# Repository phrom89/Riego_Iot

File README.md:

# Riego_Iot
Sistema de riego Iot - Proyecto Final 2023

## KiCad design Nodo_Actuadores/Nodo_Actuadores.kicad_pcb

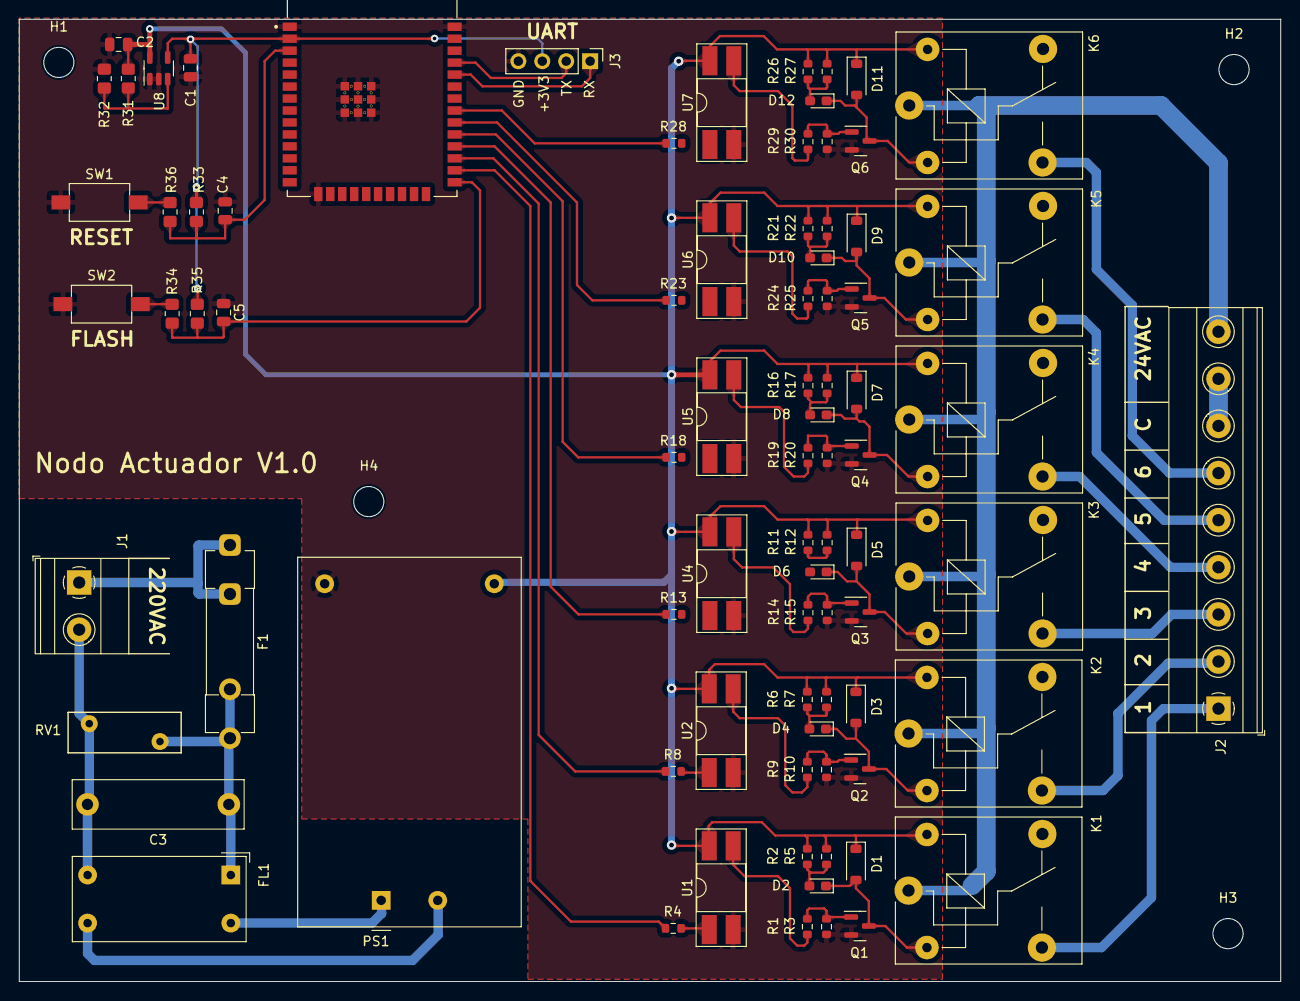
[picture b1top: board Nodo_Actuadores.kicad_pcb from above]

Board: 2 copper layers, 133.9 x 102.1 mm, 86 parts (0 on the bottom side), 59 nets.

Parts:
C1, C2, C4, C5: 0.1uF; C_0805_2012Metric
C3: 0.1uF 275V X2; C_Rect_L18.0mm_W5.0mm_P15.00mm_FKS3_FKP3
D1, D3, D5, D7, D9, D11: 1N4148W; D_SOD-123
D2, D4, D6, D8, D10, D12: TBD; LED_0603_1608Metric_Pad1.05x0.95mm_HandSolder
F1: Fuse; Fuseholder_Clip-5x20mm_Littelfuse_445-030_Inline_P20.50x5.2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
FL1: Choke 12MH 300MA 2LN TH; Choke_Schaffner_RN202-04-8.8x18.2mm
H1, H2, H3, H4: MountingHole; MountingHole_3.2mm_M3_DIN965
J1: Screw_Terminal_01x02; TerminalBlock_Phoenix_MKDS-1,5-2_1x02_P5.00mm_Horizontal
J2: Screw_Terminal_01x09_5mm; TerminalBlock_Phoenix_MKDS-1,5-9_1x09_P5.00mm_Horizontal
J3: Conn_01x04; PinHeader_1x04_P2.54mm_Vertical
K1, K2, K3, K4, K5, K6: SRD-05VDC-SL-C; Relay_SPDT_SANYOU_SRD_Series_Form_C
PS1: HLK-5M05; Converter_ACDC_HiLink_HLK-5Mxx
Q1, Q2, Q3, Q4, Q5, Q6: 2N7002; SOT-23
R1, R9, R14, R19, R24, R29: 1K; R_0603_1608Metric
R2, R4, R5, R6, R7, R8, R11, R12, R13, R16, R17, R18, R21, R22, R23, R26, R27, R28: 100; R_0603_1608Metric
R3, R10, R15, R20, R25, R30: 100K; R_0603_1608Metric
R31, R32: 100k; R_0805_2012Metric_Pad1.20x1.40mm_HandSolder
R33, R35: 10K; R_0805_2012Metric_Pad1.20x1.40mm_HandSolder
R34, R36: 220; R_0805_2012Metric_Pad1.20x1.40mm_HandSolder
RV1: 10D561KTR; RV_Disc_D12mm_W4.3mm_P7.5mm
SW1: Reset; SW_Tactile_SPST_NO_Straight_6x3,5_modificado
SW2: Flash; SW_Tactile_SPST_NO_Straight_6x3,5_modificado
U1, U2, U4, U5, U6, U7: PC817; DIP-4_W8.89mm_SMDSocket_LongPads
U3: ESP32-WROOM-32E__4MB_HIGH_TEMP_; ESP32-WROOM-32E__4MB_HIGH_TEMP
U8: R1524N033B-TR-KE; SOT-23-5

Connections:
24VAC: J2.9, K1.1, K2.1, K3.1, K4.1, K5.1, K6.1
24VAC_COMUN: J2.7, J2.8
+3V3: C1.2, J3.3, R33.1, R35.2, U3.2 (3V3), U8.4 (VOUT)
+5V: C2.2, D1.1 (K), D3.1 (K), D5.1 (K), D7.1 (K), D9.1 (K), D11.1 (K), K1.5, K2.5, K3.5, K4.5, K5.5, K6.5, PS1.4 (+Vout), R2.1, R5.1, R6.1, R7.1, R11.1, R12.1, R16.1, R17.1, R21.1, R22.1, R26.1, R27.1, R31.1, U1.4, U2.4, U4.4, U5.4, U6.4, U7.4, U8.5 (VDD)
/Fuente de alimentacion/L: F1.1, J1.1
/Fuente de alimentacion/N: C3.2, FL1.3, J1.2, RV1.2
/IN1: R4.1, U3.26 (IO4)
/IN2: R8.1, U3.27 (IO16)
/IN3: R13.1, U3.28 (IO17)
/IN4: R18.1, U3.29 (IO5)
/IN5: R23.1, U3.30 (IO18)
/IN6: R28.1, U3.31 (IO19)
GND: C1.1, C2.1, C4.2, C5.1, J3.4, PS1.3 (-Vout), Q1.2 (S), Q2.2 (S), Q3.2 (S), Q4.2 (S), Q5.2 (S), Q6.2 (S), R3.1, R10.1, R15.1, R20.1, R25.1, R30.1, R32.2, SW1.1, SW2.2, U1.2, U2.2, U3.1 (GND), U3.15 (GND), U3.38 (GND), U3.39_1 (GND), U3.39_2 (GND), U3.39_3 (GND), U3.39_4 (GND), U3.39_5 (GND), U3.39_6 (GND), U3.39_7 (GND), U3.39_8 (GND), U3.39_9 (GND), U4.2, U5.2, U6.2, U7.2, U8.1 (GND), U8.2 (GND)
unnamed: C3.1, F1.2, FL1.1, RV1.1
unnamed: D1.2 (A), D2.1 (K), K1.2, Q1.3 (D)
unnamed: D2.2 (A), R2.2, R5.2
unnamed: D3.2 (A), D4.1 (K), K2.2, Q2.3 (D)
unnamed: D4.2 (A), R6.2, R7.2
unnamed: D5.2 (A), D6.1 (K), K3.2, Q3.3 (D)
unnamed: D6.2 (A), R11.2, R12.2
unnamed: D7.2 (A), D8.1 (K), K4.2, Q4.3 (D)
unnamed: D8.2 (A), R16.2, R17.2
unnamed: D10.2 (A), R21.2, R22.2
unnamed: D9.2 (A), D10.1 (K), K5.2, Q5.3 (D)
unnamed: D11.2 (A), D12.1 (K), K6.2, Q6.3 (D)
unnamed: D12.2 (A), R26.2, R27.2
unnamed: J3.1, U3.34 (RXD0)
unnamed: J3.2, U3.35 (TXD0)
unnamed: FL1.2, PS1.1 (AC/L)
unnamed: FL1.4, PS1.2 (AC/N)
unnamed: Q1.1 (G), R1.2, R3.2
unnamed: Q2.1 (G), R9.2, R10.2
unnamed: Q3.1 (G), R14.2, R15.2
unnamed: Q4.1 (G), R19.2, R20.2
unnamed: Q5.1 (G), R24.2, R25.2
unnamed: Q6.1 (G), R29.2, R30.2
unnamed: R1.1, U1.3
unnamed: R4.2, U1.1
unnamed: R8.2, U2.1
unnamed: R9.1, U2.3
unnamed: R13.2, U4.1
unnamed: R14.1, U4.3
unnamed: R18.2, U5.1
unnamed: R19.1, U5.3
unnamed: R23.2, U6.1
unnamed: R24.1, U6.3
unnamed: R28.2, U7.1
unnamed: R29.1, U7.3
unnamed: R34.2, SW2.1
unnamed: R36.1, SW1.2
unnamed: C4.1, R33.2, R36.2, U3.3 (EN)
unnamed: C5.2, R34.1, R35.1, U3.25 (IO0)
unnamed: R31.2, R32.1, U8.3 (CE)
OUT1: J2.1, K1.3
OUT2: J2.2, K2.3
OUT3: J2.3, K3.3
OUT4: J2.4, K4.3
OUT5: J2.5, K5.3
OUT6: J2.6, K6.3

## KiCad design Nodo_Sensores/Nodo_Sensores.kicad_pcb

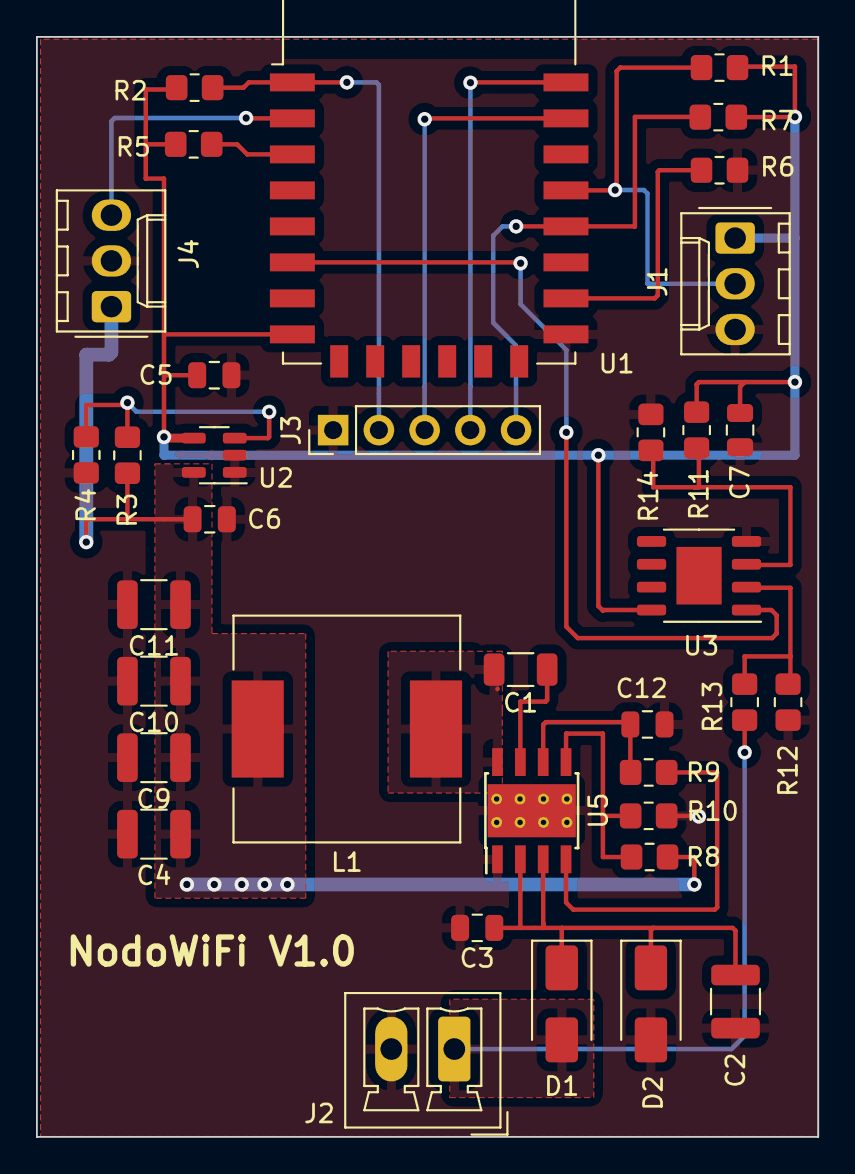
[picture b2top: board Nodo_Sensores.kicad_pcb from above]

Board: 2 copper layers, 43.4 x 61.1 mm, 36 parts (0 on the bottom side), 22 nets.

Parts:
C1: 100nF; C_1206_3216Metric
C2: 10uF; C_1210_3225Metric
C3: 220nF; C_0805_2012Metric
C4, C9, C10, C11: 22uF; C_1210_3225Metric
C5, C6, C7: 0.1uF; C_0805_2012Metric
C12: 1uF; C_0805_2012Metric
D1: SK34A; D_SMA
D2: D; D_SMA
J1, J4: Conn_01x03; Molex_KK-254_AE-6410-03A_1x03_P2.54mm_Vertical
J2: Conn_01x02; PhoenixContact_MCV_1,5_2-G-3.5_1x02_P3.50mm_Vertical
J3: Conn_01x05; PinHeader_1x05_P2.54mm_Vertical
L1: 6.8uH; L_12x12mm_H8mm
R1: 47K; R_0805_2012Metric_Pad1.20x1.40mm_HandSolder
R2, R5, R6, R7: 10K; R_0805_2012Metric_Pad1.20x1.40mm_HandSolder
R3, R4, R8, R9: 100k; R_0805_2012Metric_Pad1.20x1.40mm_HandSolder
R10: 43,2K; R_0805_2012Metric_Pad1.20x1.40mm_HandSolder
R11, R12, R14: 10k; R_0805_2012Metric_Pad1.20x1.40mm_HandSolder
R13: 20k; R_0805_2012Metric_Pad1.20x1.40mm_HandSolder
U1: ESP-12F; ESP-12E
U2: R1524N033B-TR-KE; SOT-23-5
U3: TS3702; SOIC-8-1EP_3.9x4.9mm_P1.27mm_EP2.514x3.2mm
U5: LMR33630ADDA; Texas_HSOP-8-1EP_3.9x4.9mm_P1.27mm_ThermalVias

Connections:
+3.3V: C5.2, C7.1, J1.1, R1.1, R2.1, R5.1, R7.1, R11.1, U1.8 (VCC), U2.4 (VOUT), U3.8 (V+)
+5V: C4.1, C6.2, C9.1, C10.1, C11.1, J4.1, L1.2, R3.1, R8.2, U2.5 (VDD)
/FB: R8.1, R10.2, U5.5 (FB)
/SW: C1.2, L1.1, U5.8 (SW)
/V_BAT: D1.2 (A), J2.1, R13.1
ADC_In: J4.3, U1.2 (ADC)
DQ: J1.2, R1.2, U1.19 (GPIO4)
DTR: J3.5, R7.2, U1.18 (GPIO0)
ESP_RX: J3.3, U1.21 (GPIO3/RXD)
ESP_TX: J3.4, U1.22 (GPIO1/TXD)
GND: C2.2, C3.2, C4.2, C5.1, C6.1, C7.2, C9.2, C10.2, C11.2, C12.2, D2.2 (A), J1.3, J2.2, J3.1, J4.2, R4.2, R6.2, R10.1, R12.2, R14.2, U1.15 (GND), U2.1 (GND), U2.2 (GND), U3.4 (V-), U5.1 (PGND), U5.9 (AGND)
LOW_BAT: U1.6 (GPIO12), U3.1
unnamed: C2.1, C3.1, D1.1 (K), D2.1 (K), U5.2 (VIN), U5.3 (EN)
unnamed: R5.2, U1.3 (EN)
unnamed: R6.1, U1.16 (GPIO15)
unnamed: R3.2, R4.1, U2.3 (CE)
unnamed: R11.2, R14.1, U3.3 (+)
unnamed: R12.1, R13.2, U3.2 (-)
unnamed: C1.1, U5.7 (BOOT)
unnamed: R9.1, U5.4 (PG)
unnamed: C12.1, R9.2, U5.6 (VCC)
RTS: J3.2, R2.2, U1.1 (~RST)

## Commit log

2023-06-15 Estableciendo comunicacion entre esp8266 y AWS
2023-08-01 Primer commit con proyecto Nodo sensores
2023-08-06 Se avanzó con el esquematico. Falta definir método de prog del esp y agregar protecciones
2023-09-15 modificacion sch
2023-10-17 Nodo_Sensores V1.0
2023-10-27 Nodo actuadores V1 finalizada
